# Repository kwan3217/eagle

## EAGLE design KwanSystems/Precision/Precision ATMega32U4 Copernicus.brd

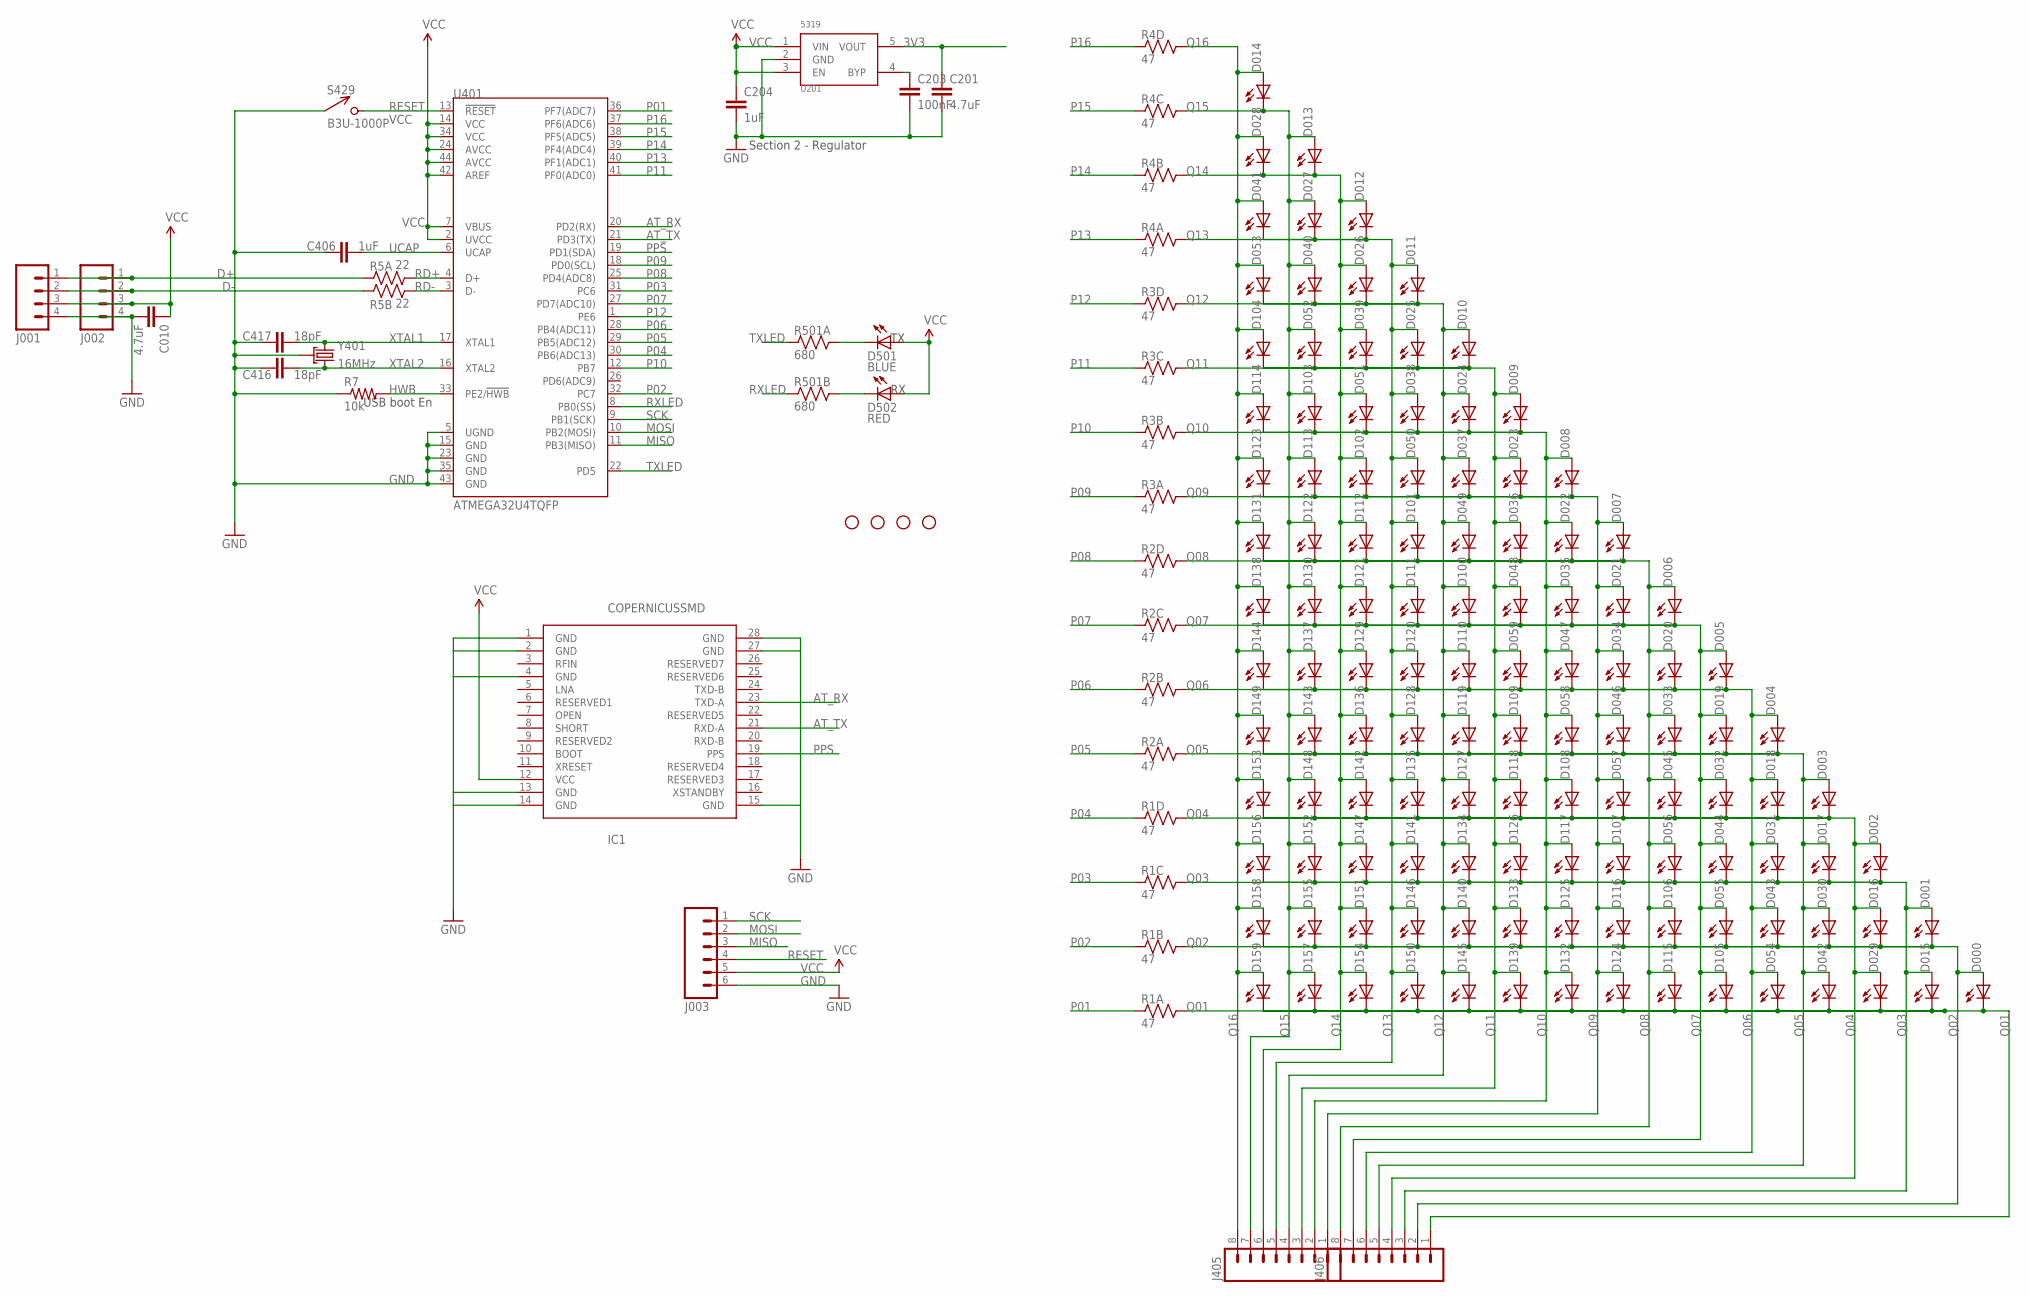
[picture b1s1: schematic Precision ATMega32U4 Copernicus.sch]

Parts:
C010: 4.7uF; 0603-CAP
C201: 4.7uF; 0402-CAP
C203: 100nF; 0402-CAP
C204: 1uF; 0402-CAP
C406: 1uF; 0603-CAP
C416, C417: 18pF; 0603-CAP
D000, D001, D002, D003, D004, D005, D006, D007, D008, D009, D010, D011, D012, D013, D014, D015, D016, D017, D018, D019, D020, D021, D022, D023, D024, D025, D026, D027, D028, D029, D030, D031, D032, D033, D034, D035, D036, D037, D038, D039, D040, D041, D042, D043, D044, D045, D046, D047, D048, D049, D050, D051, D052, D053, D054, D055, D056, D057, D058, D059, D100, D101, D102, D103, D104, D105, D106, D107, D108, D109, D110, D111, D112, D113, D114, D115, D116, D117, D118, D119, D120, D121, D122, D123, D124, D125, D126, D127, D128, D129, D130, D131, D132, D133, D134, D135, D136, D137, D138, D139, D140, D141, D142, D143, D144, D145, D146, D147, D148, D149, D150, D151, D152, D153, D154, D155, D156, D157, D158, D159: HOUR; LED-0603
D501: BLUE; LED-0603
D502: RED; LED-0603
IC1: COPERNICUSSMD; COPERNICUS
J001, J002: M04PTH; 1X04
J003: M06SIP; 1X06
J405, J406: M081X08; 1X08
JP1, JP2, JP3, JP4: STAND-OFF
R1, R2, R3, R4: 47; CRA04
R5: 22; CRA02
R7: 10k; 0603-RES
R501: 680; CRA02
S429: B3U-1000P
U201: 5319; SOT-23-5
U401: ATMEGA32U4TQFP; SPARKFUN-DIGITALIC_TQFP44
Y401: 16MHz; CRYSTAL_SMD

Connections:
3V3: C201.1, U201.5 (VOUT)
AT_RX: IC1.23 (TXD-A), U401.20 (PD2(RX))
AT_TX: IC1.21 (RXD-A), U401.21 (PD3(TX))
D+: J001.1, J002.1, R5.1
D-: J001.2, J002.2, R5.2 (1)
GND: C010.2, C201.2, C203.2, C204.2, C406.2, C416.1, C417.1, IC1.1 (GND), IC1.2 (GND), IC1.4 (GND), IC1.13 (GND), IC1.14 (GND), IC1.15 (GND), IC1.27 (GND), IC1.28 (GND), J001.4, J002.4, J003.6, R7.1, S429.P$1 (1), U201.2 (GND), U401.5 (UGND), U401.15 (GND), U401.23 (GND), U401.35 (GND), U401.43 (GND), Y401.2 (GND), Y401.4 (GND)
HWB: R7.2, U401.33 (PE2/!HWB)
MISO: J003.3, U401.11 (PB3(MISO))
MOSI: J003.2, U401.10 (PB2(MOSI))
unnamed: C203.1, U201.4 (BYP)
P01: R1.1, U401.36 (PF7(ADC7))
P02: R1.2 (1), U401.32 (PC7)
P03: R1.3 (1), U401.31 (PC6)
P04: R1.4 (1), U401.30 (PB6(ADC13))
P05: R2.1, U401.29 (PB5(ADC12))
P06: R2.2 (1), U401.28 (PB4(ADC11))
P07: R2.3 (1), U401.27 (PD7(ADC10))
P08: R2.4 (1), U401.25 (PD4(ADC8))
P09: R3.1, U401.18 (PD0(SCL))
P10: R3.2 (1), U401.12 (PB7)
P11: R3.3 (1), U401.41 (PF0(ADC0))
P12: R3.4 (1), U401.1 (PE6)
P13: R4.1, U401.40 (PF1(ADC1))
P14: R4.2 (1), U401.39 (PF4(ADC4))
P15: R4.3 (1), U401.38 (PF5(ADC5))
P16: R4.4 (1), U401.37 (PF6(ADC6))
PPS: IC1.19 (PPS), U401.19 (PD1(SDA))
Q01: D000.C, D015.C, D029.C, D042.C, D054.C, D105.C, D115.C, D124.C, D132.C, D139.C, D145.C, D150.C, D154.C, D157.C, D159.C, J406.1, R1.8 (2)
Q02: D000.A, D001.C, D016.C, D030.C, D043.C, D055.C, D106.C, D116.C, D125.C, D133.C, D140.C, D146.C, D151.C, D155.C, D158.C, J406.2, R1.7 (2)
Q03: D001.A, D002.C, D015.A, D017.C, D031.C, D044.C, D056.C, D107.C, D117.C, D126.C, D134.C, D141.C, D147.C, D152.C, D156.C, J406.3, R1.6 (2)
Q04: D002.A, D003.C, D016.A, D018.C, D029.A, D032.C, D045.C, D057.C, D108.C, D118.C, D127.C, D135.C, D142.C, D148.C, D153.C, J406.4, R1.5 (2)
Q05: D003.A, D004.C, D017.A, D019.C, D030.A, D033.C, D042.A, D046.C, D058.C, D109.C, D119.C, D128.C, D136.C, D143.C, D149.C, J406.5, R2.8 (2)
Q06: D004.A, D005.C, D018.A, D020.C, D031.A, D034.C, D043.A, D047.C, D054.A, D059.C, D110.C, D120.C, D129.C, D137.C, D144.C, J406.6, R2.7 (2)
Q07: D005.A, D006.C, D019.A, D021.C, D032.A, D035.C, D044.A, D048.C, D055.A, D100.C, D105.A, D111.C, D121.C, D130.C, D138.C, J406.7, R2.6 (2)
Q08: D006.A, D007.C, D020.A, D022.C, D033.A, D036.C, D045.A, D049.C, D056.A, D101.C, D106.A, D112.C, D115.A, D122.C, D131.C, J406.8, R2.5 (2)
Q09: D007.A, D008.C, D021.A, D023.C, D034.A, D037.C, D046.A, D050.C, D057.A, D102.C, D107.A, D113.C, D116.A, D123.C, D124.A, J405.1, R3.8 (2)
Q10: D008.A, D009.C, D022.A, D024.C, D035.A, D038.C, D047.A, D051.C, D058.A, D103.C, D108.A, D114.C, D117.A, D125.A, D132.A, J405.2, R3.7 (2)
Q11: D009.A, D010.C, D023.A, D025.C, D036.A, D039.C, D048.A, D052.C, D059.A, D104.C, D109.A, D118.A, D126.A, D133.A, D139.A, J405.3, R3.6 (2)
Q12: D010.A, D011.C, D024.A, D026.C, D037.A, D040.C, D049.A, D053.C, D100.A, D110.A, D119.A, D127.A, D134.A, D140.A, D145.A, J405.4, R3.5 (2)
Q13: D011.A, D012.C, D025.A, D027.C, D038.A, D041.C, D050.A, D101.A, D111.A, D120.A, D128.A, D135.A, D141.A, D146.A, D150.A, J405.5, R4.8 (2)
Q14: D012.A, D013.C, D026.A, D028.C, D039.A, D051.A, D102.A, D112.A, D121.A, D129.A, D136.A, D142.A, D147.A, D151.A, D154.A, J405.6, R4.7 (2)
Q15: D013.A, D014.C, D027.A, D040.A, D052.A, D103.A, D113.A, D122.A, D130.A, D137.A, D143.A, D148.A, D152.A, D155.A, D157.A, J405.7, R4.6 (2)
Q16: D014.A, D028.A, D041.A, D053.A, D104.A, D114.A, D123.A, D131.A, D138.A, D144.A, D149.A, D153.A, D156.A, D158.A, D159.A, J405.8, R4.5 (2)
RD+: R5.4 (2), U401.4 (D+)
RD-: R5.3 (2), U401.3 (D-)
RESET: J003.4, S429.P$2 (2), U401.13 (!RESET)
RXLED: R501.2 (1), U401.8 (PB0(SS))
RXLED+: D502.C, R501.3 (2)
SCK: J003.1, U401.9 (PB1(SCK))
TXLED: R501.1, U401.22 (PD5)
TXLED+: D501.C, R501.4 (2)
UCAP: C406.1, U401.6 (UCAP)
VCC: C010.1, C204.1, D501.A, D502.A, IC1.12 (VCC), J001.3, J002.3, J003.5, U201.1 (VIN), U201.3 (EN), U401.2 (UVCC), U401.7 (VBUS), U401.14 (VCC), U401.24 (AVCC), U401.34 (VCC), U401.42 (AREF), U401.44 (AVCC)
XTAL1: C417.2, U401.17 (XTAL1), Y401.1
XTAL2: C416.2, U401.16 (XTAL2), Y401.3 (2)

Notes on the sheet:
USB boot En
Section 2 - Regulator

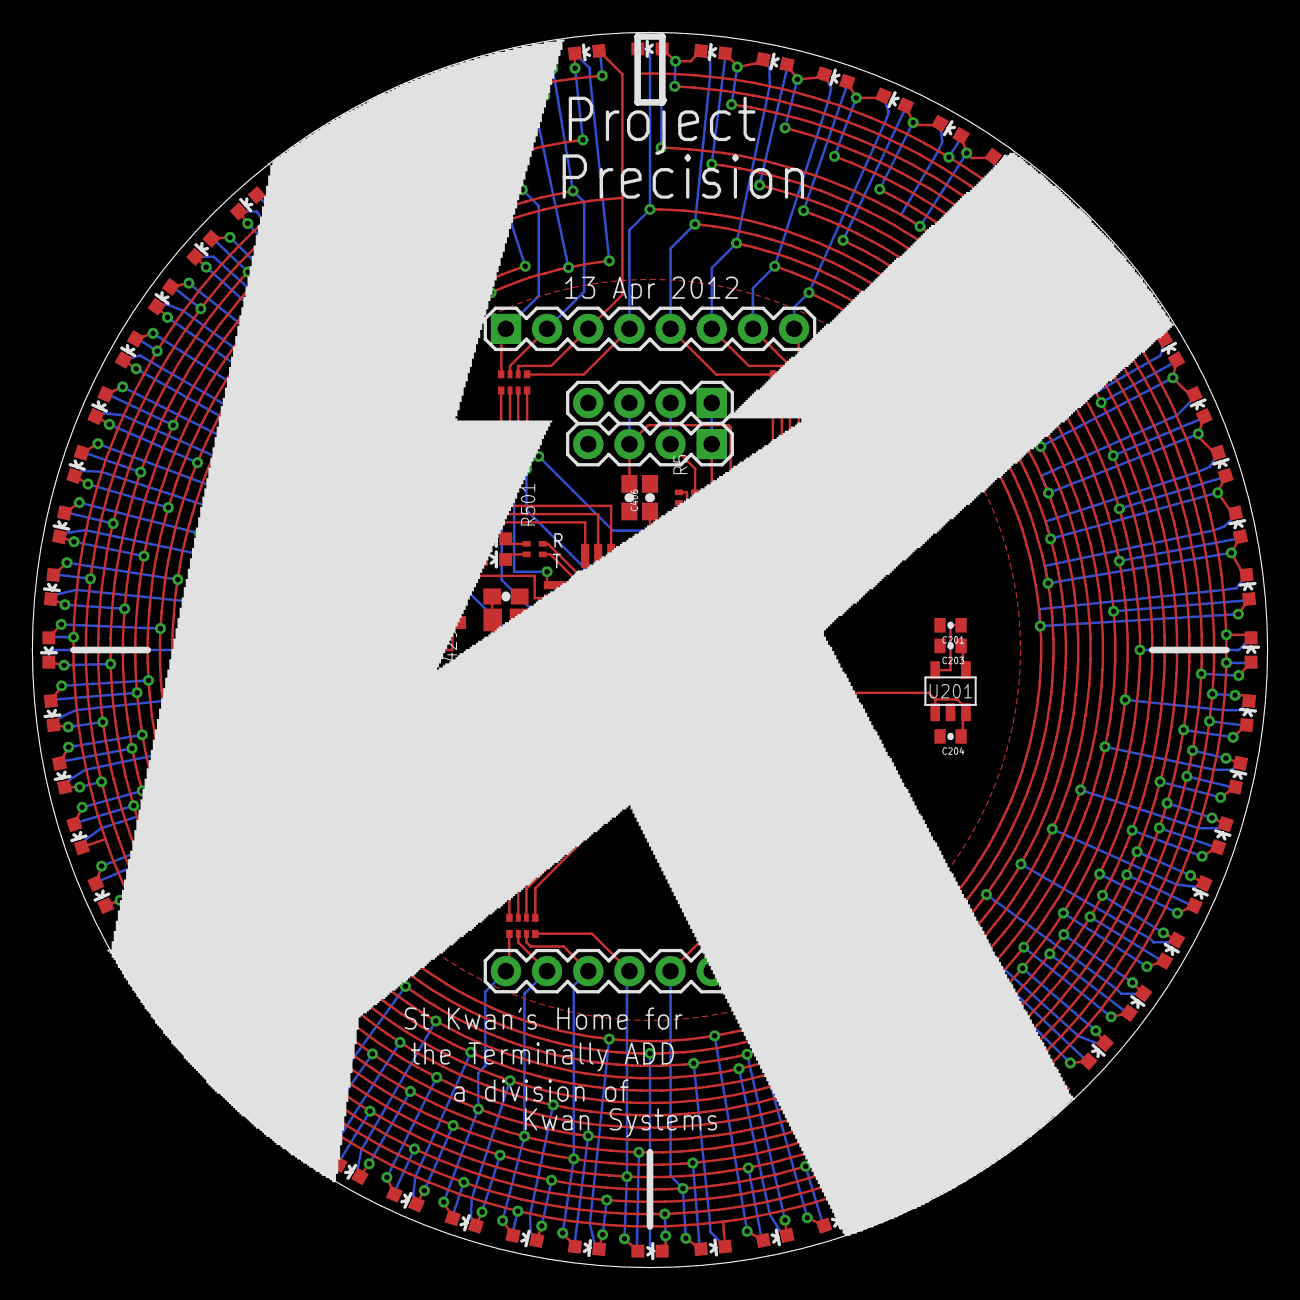
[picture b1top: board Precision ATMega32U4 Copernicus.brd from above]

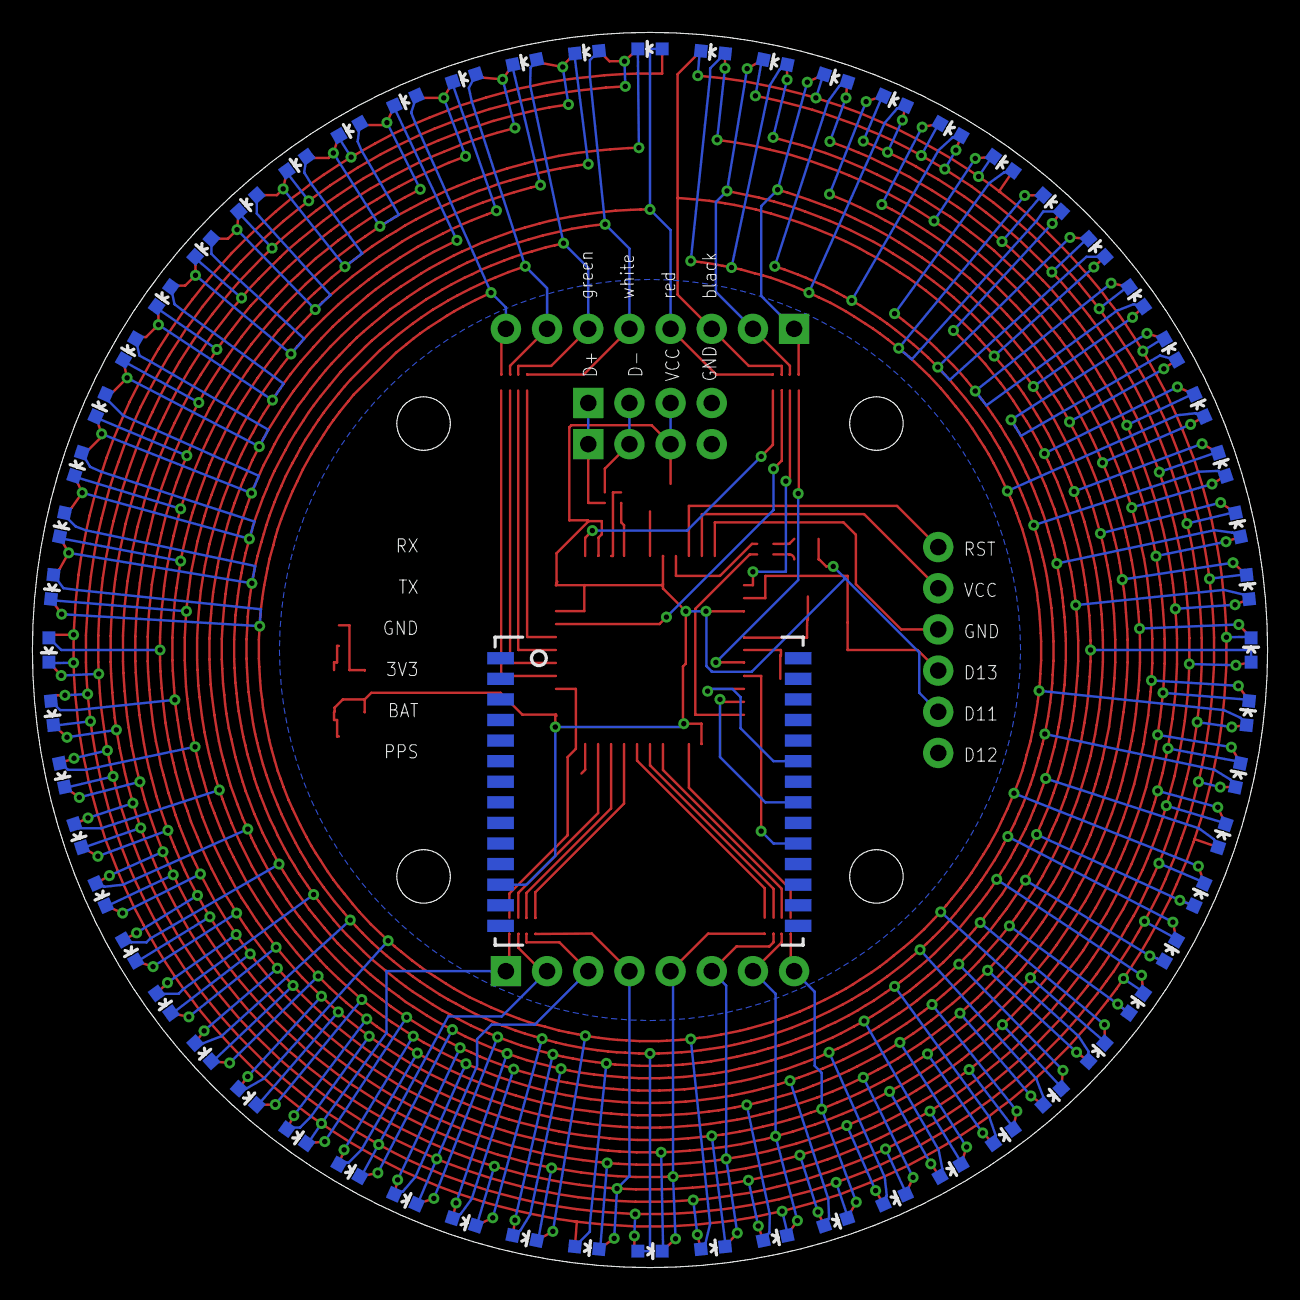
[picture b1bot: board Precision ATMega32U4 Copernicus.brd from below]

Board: 2 copper layers, 76.2 x 76.2 mm, 150 parts (61 on the bottom side), 55 nets.

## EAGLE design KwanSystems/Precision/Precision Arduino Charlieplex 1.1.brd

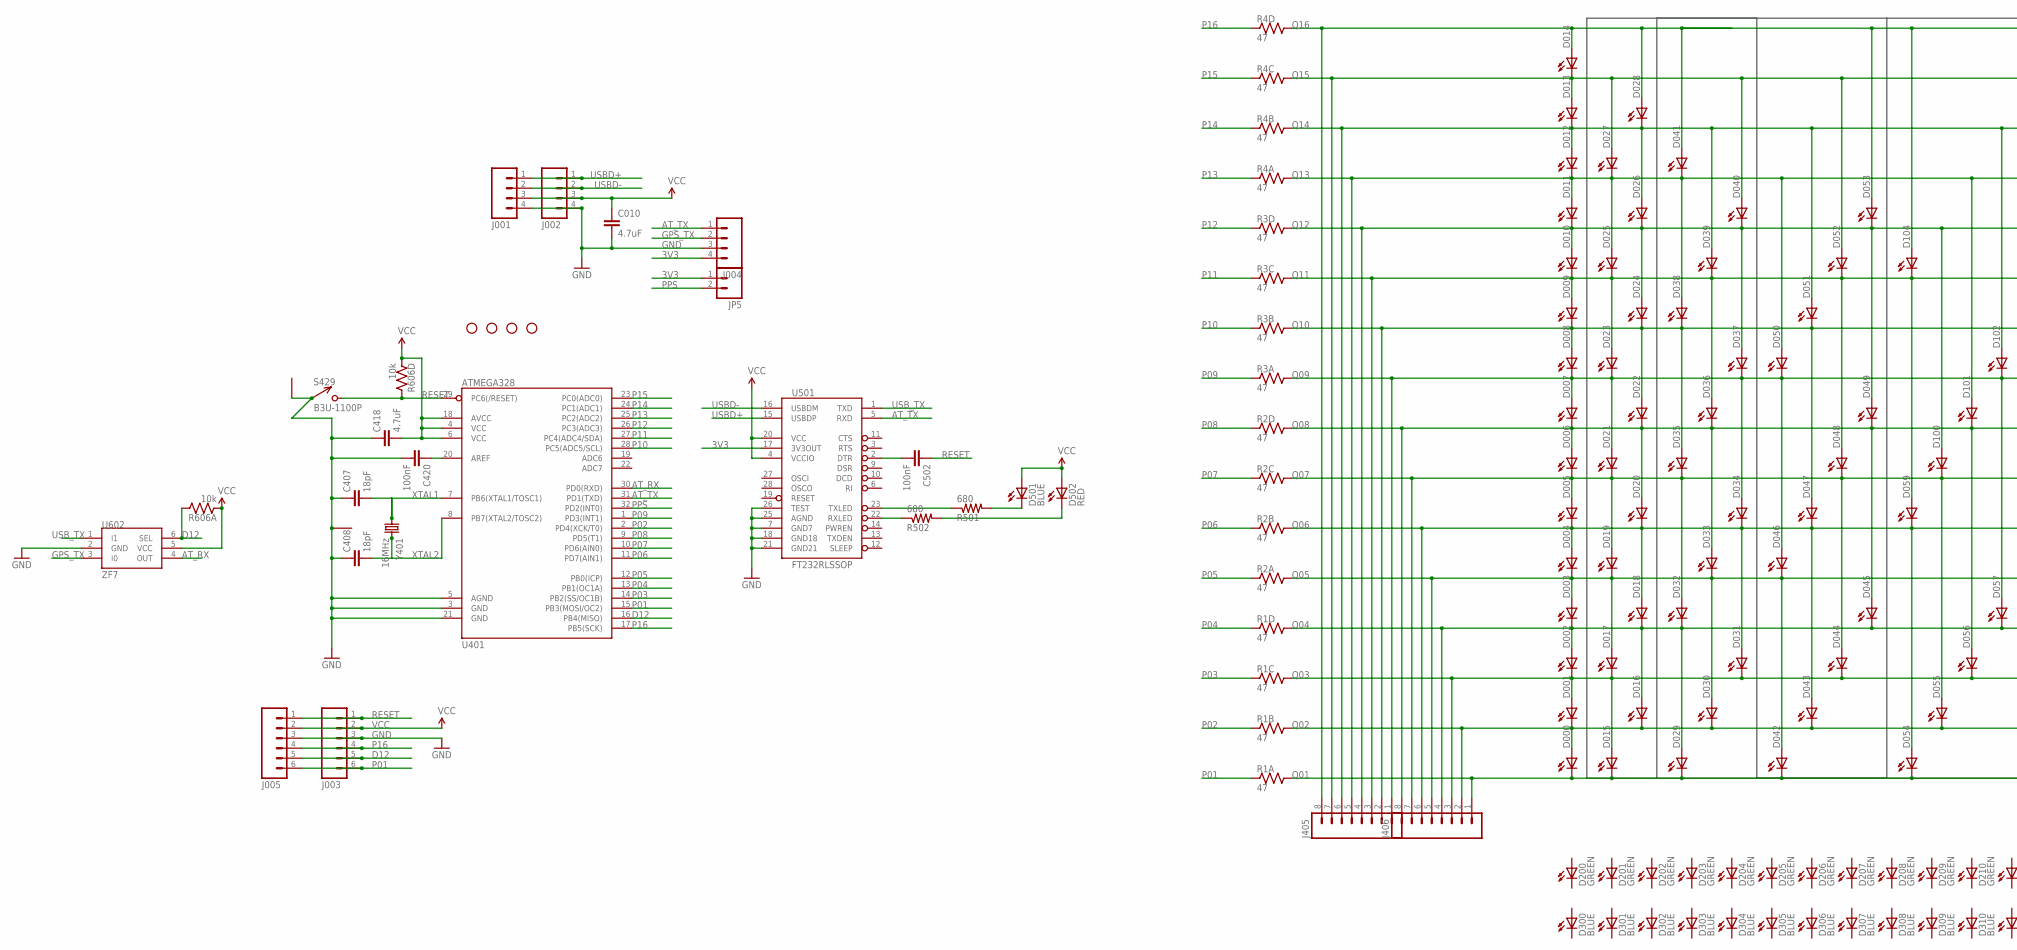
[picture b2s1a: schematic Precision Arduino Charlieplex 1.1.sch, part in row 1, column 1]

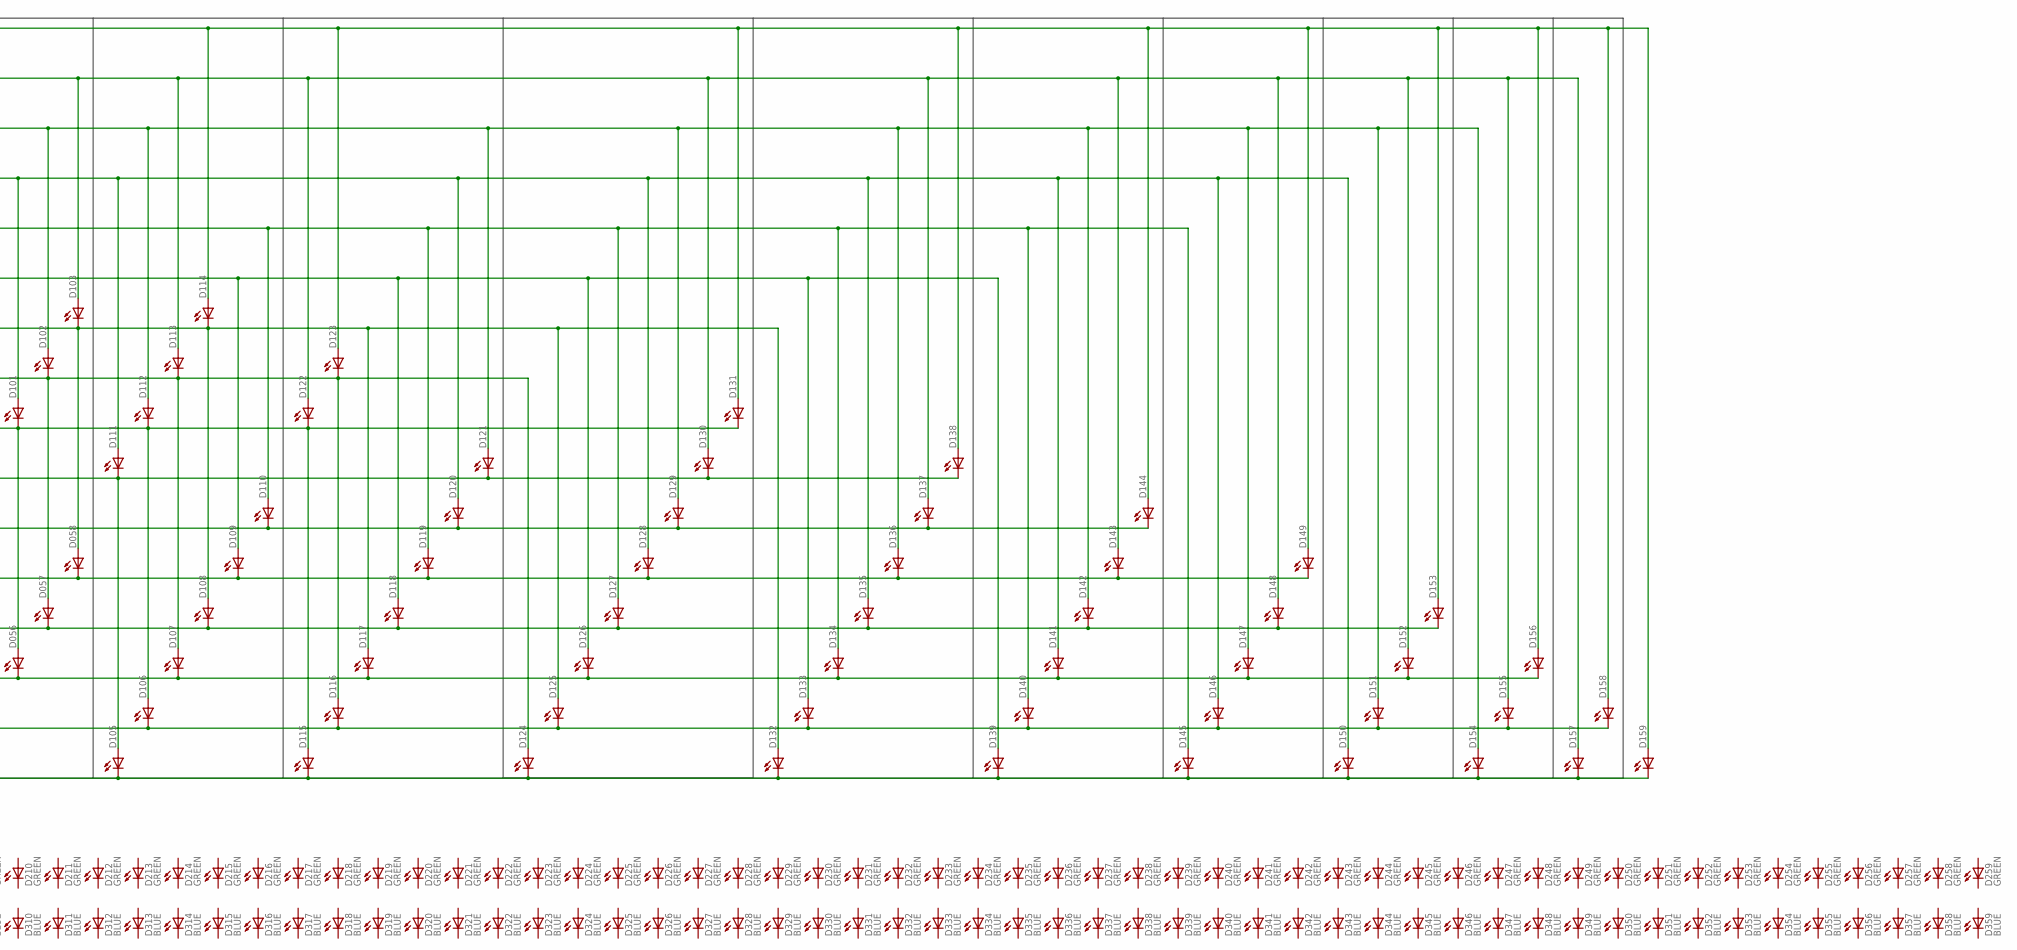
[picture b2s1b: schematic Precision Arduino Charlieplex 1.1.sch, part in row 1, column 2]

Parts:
C010, C418: 4.7uF; 0603-CAP; DIGIKEY 445-7483-1-ND
C407, C408: 18pF; 0603-CAP; DIGIKEY 478-6025-1-ND
C420, C502: 100nF; 0603-CAP; DIGIKEY 445-1316-1-ND
D000, D001, D002, D003, D004, D005, D006, D007, D008, D009, D010, D011, D012, D013, D014, D015, D016, D017, D018, D019, D020, D021, D022, D023, D024, D025, D026, D027, D028, D029, D030, D031, D032, D033, D034, D035, D036, D037, D038, D039, D040, D041, D042, D043, D044, D045, D046, D047, D048, D049, D050, D051, D052, D053, D054, D055, D056, D057, D058, D059, D502: RED; LED-0603; DIGIKEY 754-1359-1-ND
D100, D101, D102, D103, D104, D105, D106, D107, D108, D109, D110, D111, D112, D113, D114, D115, D116, D117, D118, D119, D120, D121, D122, D123, D124, D125, D126, D127, D128, D129, D130, D131, D132, D133, D134, D135, D136, D137, D138, D139, D140, D141, D142, D143, D144, D145, D146, D147, D148, D149, D150, D151, D152, D153, D154, D155, D156, D157, D158, D159: YELLOW; LED-0603; DIGIKEY 754-1124-1-ND
D200, D201, D202, D203, D204, D205, D206, D207, D208, D209, D210, D211, D212, D213, D214, D215, D216, D217, D218, D219, D220, D221, D222, D223, D224, D225, D226, D227, D228, D229, D230, D231, D232, D233, D234, D235, D236, D237, D238, D239, D240, D241, D242, D243, D244, D245, D246, D247, D248, D249, D250, D251, D252, D253, D254, D255, D256, D257, D258, D259: GREEN; LED-0603; DIGIKEY 350-2036-1-ND
D300, D301, D302, D303, D304, D305, D306, D307, D308, D309, D310, D311, D312, D313, D314, D315, D316, D317, D318, D319, D320, D321, D322, D323, D324, D325, D326, D327, D328, D329, D330, D331, D332, D333, D334, D335, D336, D337, D338, D339, D340, D341, D342, D343, D344, D345, D346, D347, D348, D349, D350, D351, D352, D353, D354, D355, D356, D357, D358, D359, D501: BLUE; LED-0603; DIGIKEY 350-2037-1-ND
J001, J002, J004: M04PTH; 1X04; DIGIKEY $NOPART
J003, J005: M06SIP; 1X06; DIGIKEY $NOPART
J405, J406: M081X08; 1X08; DIGIKEY $NOPART
JP1, JP2, JP3, JP4: STAND-OFF; DIGIKEY $NOPART
JP5: M02PTH; 1X02; DIGIKEY $NOPART
R1, R2, R3, R4: 47; CRA04; DIGIKEY CRA4S847CT-ND
R501, R502: 680; 0603-RES; DIGIKEY P680GCT-ND
R606: 10k; CRA04; DIGIKEY CRA4S810KCT-ND
S429: B3U-1100P; DIGIKEY SW1021CT-ND
U401: ATMEGA328; TQFP32-08; DIGIKEY ATMEGA328P-15AZCT-ND
U501: FT232RLSSOP; SSOP28DB; DIGIKEY 768-1007-1-ND
U602: ZF7; SC-70-6; DIGIKEY NC7SZ157P6XCT-ND
Y401: 16MHz; CRYSTAL_SMD; DIGIKEY 887-1319-1-ND

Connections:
3V3: J004.4, JP5.1, U501.17 (3V3OUT)
AREF: C420.1, U401.20 (AREF)
AT_RX: U401.30 (PD0(RXD)), U602.4 (OUT)
AT_TX: J004.1, U401.31 (PD1(TXD)), U501.5 (RXD)
D12: J003.5, J005.5, R606.8 (2), U401.16 (PB4(MISO)), U602.6 (SEL)
GND: C010.2, C407.1, C408.1, C418.1, C420.2, J001.4, J002.4, J003.3, J004.3, J005.3, S429.P$1 (1), S429.P$3 (1), U401.3 (GND), U401.5 (AGND), U401.21 (GND), U501.7 (GND7), U501.18 (GND18), U501.21 (GND21), U501.25 (AGND), U501.26 (TEST), U602.2 (GND), Y401.2 (1), Y401.4 (1)
GPS_TX: J004.2, U602.3 (I0)
unnamed: C502.2, U501.2 (DTR)
unnamed: D501.C, R501.2
unnamed: R501.1, U501.23 (TXLED)
unnamed: R502.1, U501.22 (RXLED)
unnamed: D502.C, R502.2
P01: J003.6, J005.6, R1.1, U401.15 (PB3(MOSI/OC2))
P02: R1.2 (1), U401.2 (PD4(XCK/T0))
P03: R1.3 (1), U401.14 (PB2(SS/OC1B))
P04: R1.4 (1), U401.13 (PB1(OC1A))
P05: R2.1, U401.12 (PB0(ICP))
P06: R2.2 (1), U401.11 (PD7(AIN1))
P07: R2.3 (1), U401.10 (PD6(AIN0))
P08: R2.4 (1), U401.9 (PD5(T1))
P09: R3.1, U401.1 (PD3(INT1))
P10: R3.2 (1), U401.28 (PC5(ADC5/SCL))
P11: R3.3 (1), U401.27 (PC4(ADC4/SDA))
P12: R3.4 (1), U401.26 (PC3(ADC3))
P13: R4.1, U401.25 (PC2(ADC2))
P14: R4.2 (1), U401.24 (PC1(ADC1))
P15: R4.3 (1), U401.23 (PC0(ADC0))
P16: J003.4, J005.4, R4.4 (1), U401.17 (PB5(SCK))
PPS: JP5.2, U401.32 (PD2(INT0))
Q01: D000.C, D015.C, D029.C, D042.C, D054.C, D105.C, D115.C, D124.C, D132.C, D139.C, D145.C, D150.C, D154.C, D157.C, D159.C, J406.1, R1.8 (2)
Q02: D000.A, D001.C, D016.C, D030.C, D043.C, D055.C, D106.C, D116.C, D125.C, D133.C, D140.C, D146.C, D151.C, D155.C, D158.C, J406.2, R1.7 (2)
Q03: D001.A, D002.C, D015.A, D017.C, D031.C, D044.C, D056.C, D107.C, D117.C, D126.C, D134.C, D141.C, D147.C, D152.C, D156.C, J406.3, R1.6 (2)
Q04: D002.A, D003.C, D016.A, D018.C, D029.A, D032.C, D045.C, D057.C, D108.C, D118.C, D127.C, D135.C, D142.C, D148.C, D153.C, J406.4, R1.5 (2)
Q05: D003.A, D004.C, D017.A, D019.C, D030.A, D033.C, D042.A, D046.C, D058.C, D109.C, D119.C, D128.C, D136.C, D143.C, D149.C, J406.5, R2.8 (2)
Q06: D004.A, D005.C, D018.A, D020.C, D031.A, D034.C, D043.A, D047.C, D054.A, D059.C, D110.C, D120.C, D129.C, D137.C, D144.C, J406.6, R2.7 (2)
Q07: D005.A, D006.C, D019.A, D021.C, D032.A, D035.C, D044.A, D048.C, D055.A, D100.C, D105.A, D111.C, D121.C, D130.C, D138.C, J406.7, R2.6 (2)
Q08: D006.A, D007.C, D020.A, D022.C, D033.A, D036.C, D045.A, D049.C, D056.A, D101.C, D106.A, D112.C, D115.A, D122.C, D131.C, J406.8, R2.5 (2)
Q09: D007.A, D008.C, D021.A, D023.C, D034.A, D037.C, D046.A, D050.C, D057.A, D102.C, D107.A, D113.C, D116.A, D123.C, D124.A, J405.1, R3.8 (2)
Q10: D008.A, D009.C, D022.A, D024.C, D035.A, D038.C, D047.A, D051.C, D058.A, D103.C, D108.A, D114.C, D117.A, D125.A, D132.A, J405.2, R3.7 (2)
Q11: D009.A, D010.C, D023.A, D025.C, D036.A, D039.C, D048.A, D052.C, D059.A, D104.C, D109.A, D118.A, D126.A, D133.A, D139.A, J405.3, R3.6 (2)
Q12: D010.A, D011.C, D024.A, D026.C, D037.A, D040.C, D049.A, D053.C, D100.A, D110.A, D119.A, D127.A, D134.A, D140.A, D145.A, J405.4, R3.5 (2)
Q13: D011.A, D012.C, D025.A, D027.C, D038.A, D041.C, D050.A, D101.A, D111.A, D120.A, D128.A, D135.A, D141.A, D146.A, D150.A, J405.5, R4.8 (2)
Q14: D012.A, D013.C, D026.A, D028.C, D039.A, D051.A, D102.A, D112.A, D121.A, D129.A, D136.A, D142.A, D147.A, D151.A, D154.A, J405.6, R4.7 (2)
Q15: D013.A, D014.C, D027.A, D040.A, D052.A, D103.A, D113.A, D122.A, D130.A, D137.A, D143.A, D148.A, D152.A, D155.A, D157.A, J405.7, R4.6 (2)
Q16: D014.A, D028.A, D041.A, D053.A, D104.A, D114.A, D123.A, D131.A, D138.A, D144.A, D149.A, D153.A, D156.A, D158.A, D159.A, J405.8, R4.5 (2)
RESET: C502.1, J003.1, J005.1, R606.5 (2), S429.P$2 (2), U401.29 (PC6(/RESET))
USBD+: J001.1, J002.1, U501.15 (USBDP)
USBD-: J001.2, J002.2, U501.16 (USBDM)
USB_TX: U501.1 (TXD), U602.1 (I1)
VCC: C010.1, C418.2, D501.A, D502.A, J001.3, J002.3, J003.2, J005.2, R606.1, R606.4 (1), U401.4 (VCC), U401.6 (VCC), U401.18 (AVCC), U501.4 (VCCIO), U501.20 (VCC), U602.5 (VCC)
XTAL1: C407.2, U401.7 (PB6(XTAL1/TOSC1)), Y401.1
XTAL2: C408.2, U401.8 (PB7(XTAL2/TOSC2)), Y401.3 (2)

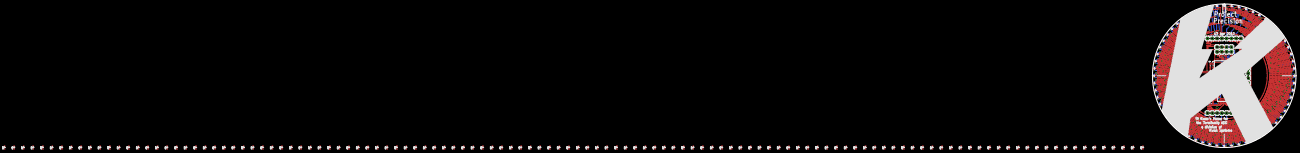
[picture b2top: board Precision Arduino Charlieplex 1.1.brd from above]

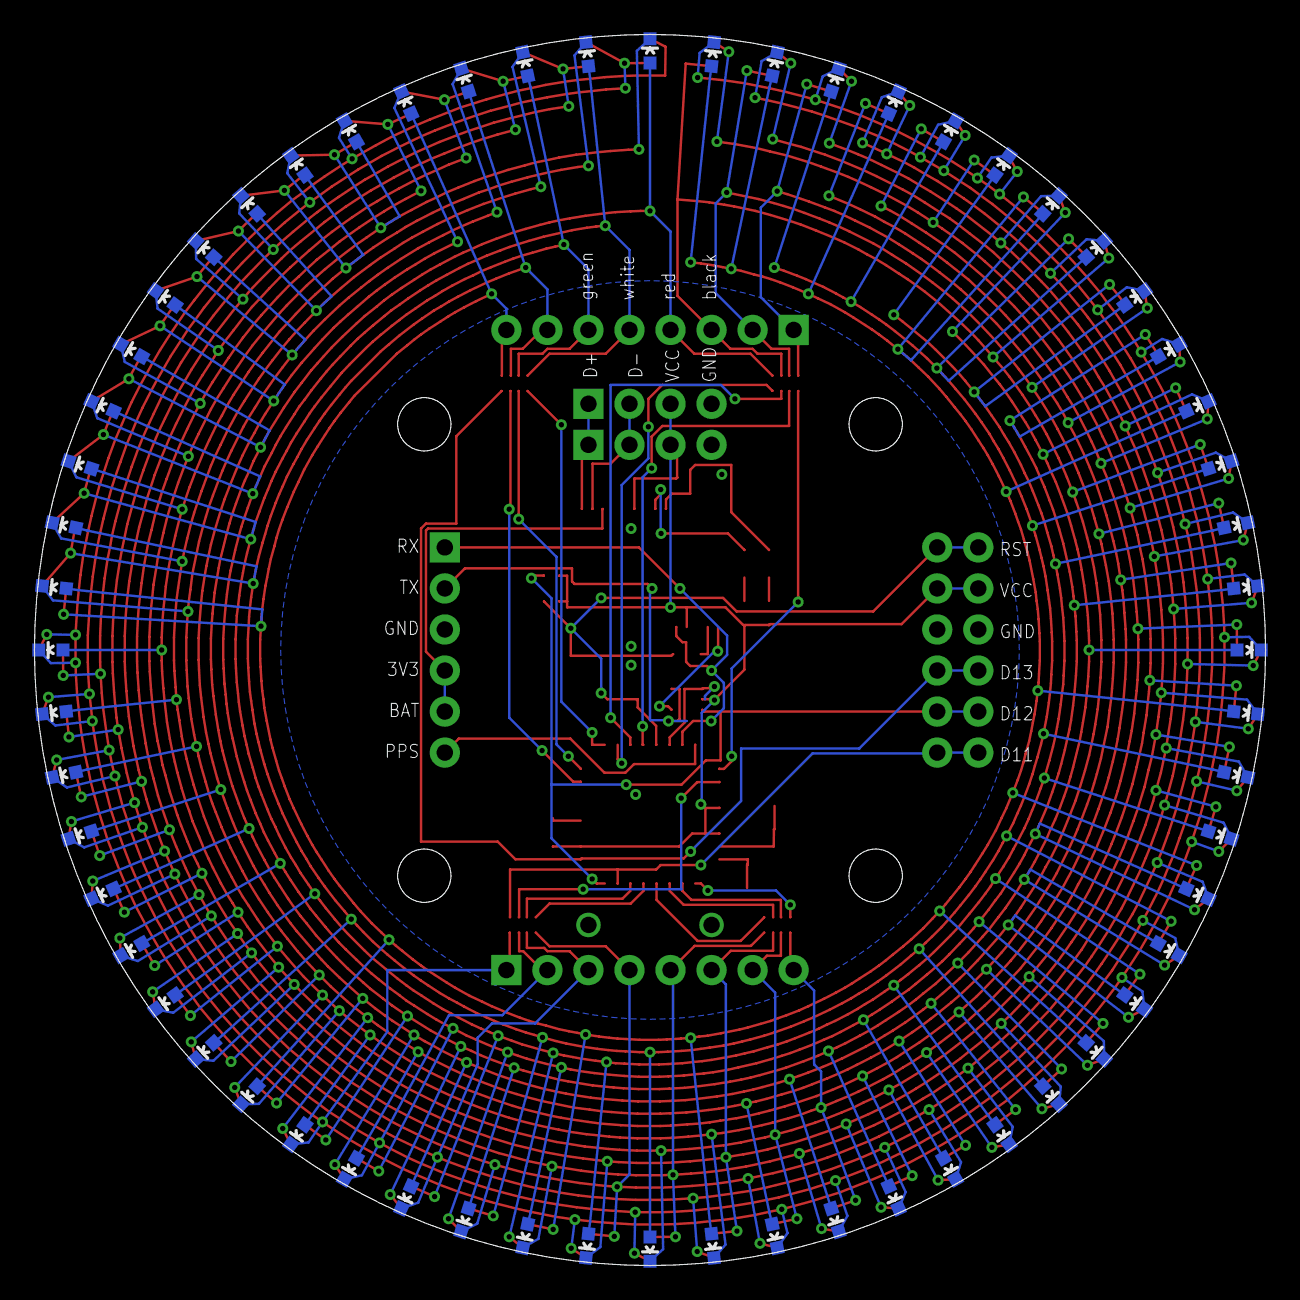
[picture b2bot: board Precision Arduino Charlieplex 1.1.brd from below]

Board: 2 copper layers, 76.2 x 76.2 mm, 272 parts (60 on the bottom side), 52 nets.

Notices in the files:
parts and their libraries:
SparkFun-DigitalIC: Licensing: CC v3.0 Share-Alike You are welcome to use this library for commercial purposes.
